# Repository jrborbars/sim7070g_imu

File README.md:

# sim7070g_imu
Sim7070g custom board with imu + batt

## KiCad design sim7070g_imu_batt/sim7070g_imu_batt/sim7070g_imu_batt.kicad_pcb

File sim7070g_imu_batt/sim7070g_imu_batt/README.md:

# sim7070g_imu_batt — build outputs (regenerate, do not hand-edit)

This folder holds circuit-synth outputs for the 45x35mm daughterboard:
SIM7070G OpenCPU + LSM6DSV16X + ETA6095 (~1A) + 1S LiPo solder pads.

## Regenerate (from repo root, project .venv = Python 3.14.x, no pins)

KICAD_SYMBOL_DIR="./sim7070g_imu_batt:/Applications/KiCad/KiCad.app/Contents/SharedSupport/symbols" \
./.venv/bin/python -c "import sim7070g_imu_batt.board as b; c=b.board(); c.generate_kicad_netlist('sim7070g_imu_batt/sim7070g_imu_batt.net'); print(c.generate_text_netlist()[:2000])"

BOM:

KICAD_SYMBOL_DIR="./sim7070g_imu_batt:/Applications/KiCad/KiCad.app/Contents/SharedSupport/symbols" \
./.venv/bin/python -c "import sim7070g_imu_batt.board as b; c=b.board(); print(c.generate_bom(project_name='sim7070g_imu_batt'))"

## KiCad workflow (schematic-first, OSS synth has no licensed PCB gen)

Workaround baked into `main.py` (`ensure_pin_number_preference`, runs on
every generation): upstream `circuit_synth/kicad/sch_gen/circuit_loader.py`
identifies pins by NAME first; stock C/R/L pins have empty names and power
pins repeat names, collapsing labels onto pin 1 (102 shorts/floats in KiCad's
own netlist, e.g. C1.1 VBAT->GND). `main.py` rewrites the installed loader
(idempotent no-op once upstream fixes it) to prefer pin NUMBER; after that
KiCad's netlist matches circuit-synth's on all 164 pins (0 real problems,
verified with `kicad-cli sch export netlist` + `cmp_netlists.py`).
Re-create the venv any time (Python 3.14.x, unpinned, pip resolves) — the
fix re-applies automatically. Only GND is exempted from power-symbol
rendering (`Net("GND", is_power=False)` in `board.py`) because the GND
symbol carries no connection semantics beyond the label here.

1. Open `sim7070g_imu_batt.kicad_pro` in KiCad.
2. Symbol libs (`sym-lib-table`): sim7070g / eta6095 / lsm6dsv16x (local
   `.kicad_sym` in this folder) + KiCad stock. Footprints (`fp-lib-table`):
   `footprints.pretty/` (local) + KiCad stock.
3. `LSM6DSV16X_LGA14.kicad_mod` is real geometry from SnapEDA
   XDCR_LSM6DSV16XTR as built in lsm6dsv16x-xiao (verify vs ST datasheet
   mech table before fab).
4. `*_PLACEHOLDER.kicad_mod` files are DO-NOT-FAB outlines only. Draw true
   `SIM7070G_LCC_LGA68` (24x24mm 68-pin LCC+LGA + 0.3mm thermal-via array,
   tented/plugged, per SIM7070 HW Design V1.05), `NanoSIM_PushPush` (MPN
   pads + DET switch), `USB-C-16P` (MPN pads + shell), `BAT_SolderPads`
   (wire-gauge pads + NPTH strain relief) before layout, then replace the
   footprint links in `board.py`.
5. Import `sim7070g_imu_batt.net` into a new 4-layer board
   (L1 Sig / L2 GND continuous / L3 PWR / L4 Sig, 1.6mm FR4) sized 45x35mm
   with 0.6mm castellated edge (TXD/RXD, USB_DP/DM, PWRKEY, RESET_N, BOOT,
   CHG_STAT, BAT+, GND). Layout rules: VBAT 1uF+TVS <2mm then 2x100uF
   <10mm on 1.0-1.5mm copper; RF L1 ref L2, Pi at ANT (series 0R, shunts
   DNP), keepout 3xW, 50R width = TRACE_W_50R_MM tuned to fab + VNA;
   USB 90R dL<0.15mm; SIM module->ESDA6V1->holder <100mm, 100nF+22pF at
   VSIM, DET 10k PU DNP; I2C 4.7k to 1V8; INT via 0R DNP to wake GPIOs.

## Locked electrical facts

ETA6095 (datasheet V1.9, 8p): NO TS/NTC, NO JEITA, NO SYS/power-path.
ISET 0.8V (150k=1.2A, 82k=2A) -> 180k ~= 1A for 1000mAh 1C. CV 4.21V,
precond 2.9V/200mA, term 130mA, recharge -160mV, STAT low=chg/Hi-Z=done,
OTG=GND forces buck. SIM7070G VBAT tied to BAT node for 2A bursts.
VDDIO=1.8V from VDD_EXT reference. MAX17048 + NTC 10k footprints DNP.

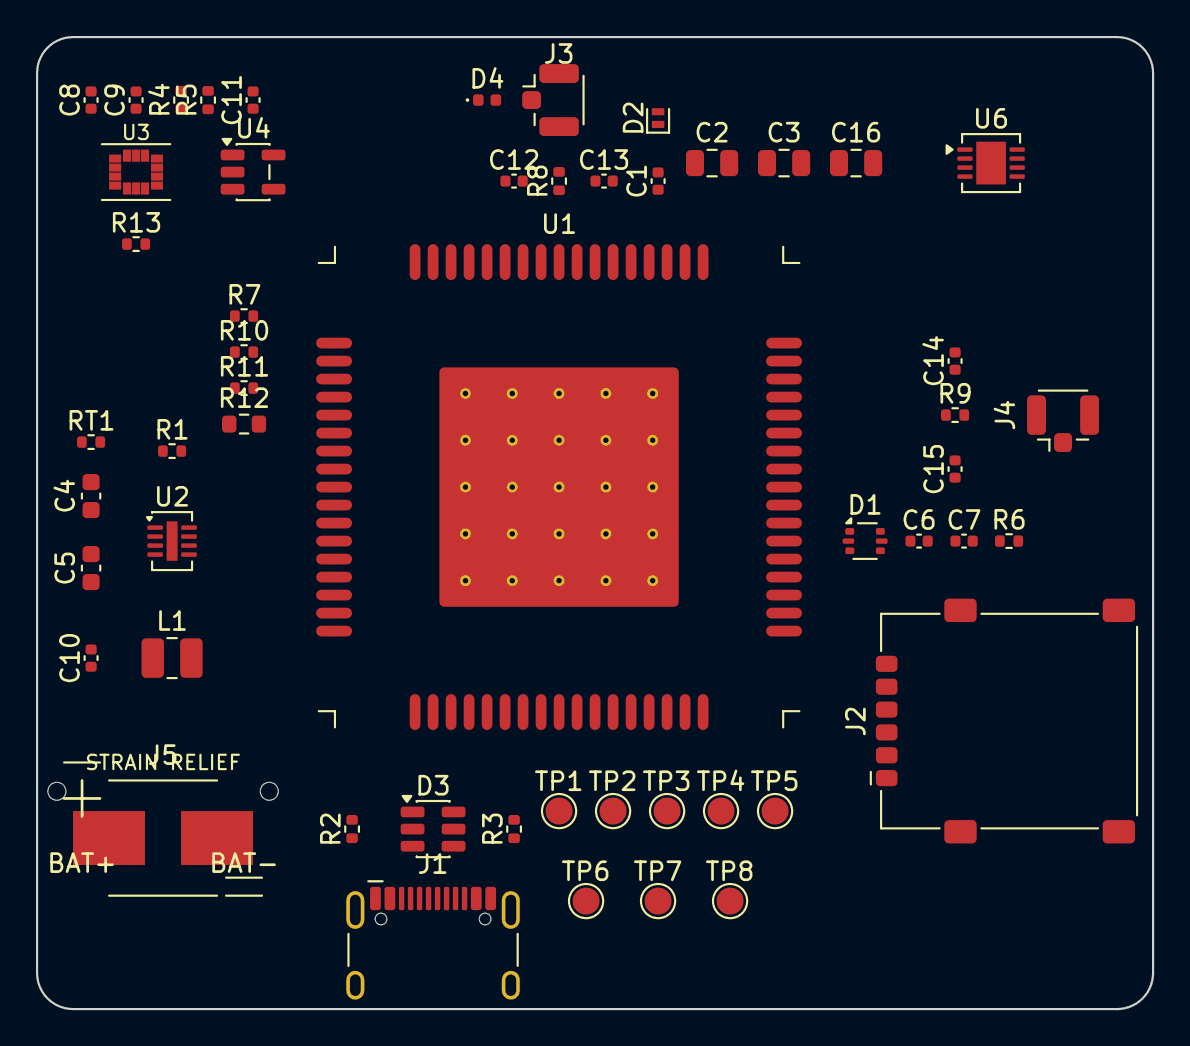
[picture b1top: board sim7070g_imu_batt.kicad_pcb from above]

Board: 4 copper layers, 62.0 x 54.0 mm, 53 parts (0 on the bottom side), 36 nets, no tracks yet.

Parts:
C1, C9, C10, C11: 1uF; C_0402_1005Metric
C2, C3, C16: 100uF; C_0805_2012Metric
C4, C5: 22uF; C_0603_1608Metric
C6, C8: 100nF; C_0402_1005Metric
C7: 22pF; C_0402_1005Metric
C12, C13, C14, C15: DNP_SHUNT; C_0402_1005Metric
D1: ESDA6V1; SOT-666
D2: TVS_PESDHC2FD4V5B; D_SOD-882
D3: USBLC6-2P6; SOT-23-6
D4: TVS_LOWCAP_ANT; D_0402_1005Metric
J1: USB-C-16P; USB_C_Receptacle_HCTL_HC-TYPE-C-16P-01A
J2: NanoSIM; NanoSIM_GCT_SIM8060-6-1
J3: U.FL_LTE; U.FL_Hirose_U.FL-R-SMT-1_Vertical
J4: U.FL_GNSS; U.FL_Hirose_U.FL-R-SMT-1_Vertical
J5: BAT_SOLDER_PADS; BAT_SolderPads
L1: 2.2uH; L_1008_2520Metric
R1: 180k; R_0402_1005Metric
R2, R3: 5.1k; R_0402_1005Metric
R4, R5: 1k; R_0402_1005Metric
R6, R13: 10k; R_0402_1005Metric
R7: 0R_JMP_GND; R_0402_1005Metric
R8, R9, R10, R11: 0R; R_0402_1005Metric
R12: 0R; R_0603_1608Metric
RT1: NTC_10k_B3380; R_0402_1005Metric
TP1: TP_PWRKEY; TestPoint_Pad_D1.5mm
TP2: TP_UART1_TXD; TestPoint_Pad_D1.5mm
TP3: TP_UART1_RXD; TestPoint_Pad_D1.5mm
TP4: TP_DEBUG_TXD; TestPoint_Pad_D1.5mm
TP5: TP_DEBUG_RXD; TestPoint_Pad_D1.5mm
TP6: TP_STATUS; TestPoint_Pad_D1.5mm
TP7: TP_CHG_STAT; TestPoint_Pad_D1.5mm
TP8: TP_VDD_EXT; TestPoint_Pad_D1.5mm
U1: SIM7070G; SIM7070G_LCC_LGA68
U2: ETA6095; DFN-8-1EP_2x3mm_P0.5mm_EP0.61x2.2mm
U3: LSM6DSV16X; LSM6DSV16X_LGA14
U4: NanoIq_LDO_2V5; SOT-23-5
U6: MAX17048_DNP; DFN-8-1EP_3x3mm_P0.5mm_EP1.65x2.38mm

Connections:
/ANT_GNSS: C14.1, R9.1, U1.53
/ANT_GNSS_MID: C15.1, J4.1, R9.2
/ANT_LTE: C12.1, D4.1, R8.1, U1.60
/ANT_LTE_MID: C13.1, J3.1, R8.2
/BAT_PACK: J5.1, R12.1
/BOOT_CFG: R7.1, U1.6
/CC1: J1.A5, R2.2
/CC2: J1.B5, R3.2
/CHG_STAT: TP7.1, U2.4
/DEBUG_RXD: TP5.1, U1.22
/DEBUG_TXD: TP4.1, U1.23
/GND: C1.2, C2.2, C3.2, C4.2, C5.2, C6.2, C7.2, C8.2, C9.2, C11.2, C12.2, C13.2, C14.2, C15.2, C16.2, D1.2, D2.2, D3.2, D4.2, J1.A1, J1.A12, J1.B1, J1.B12, J1.SH, J2.5, J2.6, J2.SH, J3.2, J4.2, J5.2, R1.2, R2.1, R3.1, R7.2, RT1.2, U1.2, U2.2, U2.6, U2.8, U3.6, U3.7, U4.2, U6.4
/IMU_VDD: C8.1, C9.1, C11.1, U3.8, U4.5
/INT1: R10.1, U3.4
/INT1_M: R10.2, U1.20
/INT2: R11.1, U3.9
/INT2_M: R11.2, U1.21
/ISET: R1.1, U2.3
/PWRKEY: TP1.1, U1.1
/SCL: R5.2, U1.38, U3.13, U6.6
/SDA: R4.2, U1.37, U3.14, U6.5
/SIM_CLK: D1.1, J2.3, U1.32
/SIM_DATA: D1.3, J2.7, U1.31
/SIM_DET: D1.6, J2.SW, R6.2, U1.67
/SIM_RST: D1.4, J2.2, U1.33
/STATUS: TP6.1, U1.66
/SW_CHG: L1.1, U2.7
/UART1_DTR: R13.2, U1.3
/UART1_RXD: TP3.1, U1.10
/UART1_TXD: TP2.1, U1.9
/USB_5V: C4.1, C5.1, D3.5, J1.A4, J1.A9, J1.B4, J1.B9, U1.24, U2.5
/USB_DM: D3.3, D3.4, J1.A7, J1.B7, U1.28
/USB_DP: D3.1, D3.6, J1.A6, J1.B6, U1.27
/VBAT: C1.1, C2.1, C3.1, C10.1, C16.1, D2.1, L1.2, R12.2, RT1.1, U1.55, U2.1, U4.1, U4.3, U6.3, U6.8
/VDD_1V8: R4.1, R5.1, R6.1, R13.1, TP8.1, U1.15, U3.5
/VSIM: C6.1, C7.1, D1.5, J2.1, U1.30

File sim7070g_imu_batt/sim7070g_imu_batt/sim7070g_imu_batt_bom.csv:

"Refs","Value","Footprint","Qty","DNP"
"C1","1uF","Capacitor_SMD:C_0402_1005Metric","1",""
"C2","100uF","Capacitor_SMD:C_0805_2012Metric","1",""
"C3","100uF","Capacitor_SMD:C_0805_2012Metric","1",""
"C4","22uF","Capacitor_SMD:C_0603_1608Metric","1",""
"C5","22uF","Capacitor_SMD:C_0603_1608Metric","1",""
"C6","100nF","Capacitor_SMD:C_0402_1005Metric","1",""
"C7","22pF","Capacitor_SMD:C_0402_1005Metric","1",""
"C8","100nF","Capacitor_SMD:C_0402_1005Metric","1",""
"C9","1uF","Capacitor_SMD:C_0402_1005Metric","1",""
"C10","1uF","Capacitor_SMD:C_0402_1005Metric","1",""
"C11","1uF","Capacitor_SMD:C_0402_1005Metric","1",""
"C12","DNP_SHUNT","Capacitor_SMD:C_0402_1005Metric","1","true"
"C13","DNP_SHUNT","Capacitor_SMD:C_0402_1005Metric","1","true"
"C14","DNP_SHUNT","Capacitor_SMD:C_0402_1005Metric","1","true"
"C15","DNP_SHUNT","Capacitor_SMD:C_0402_1005Metric","1","true"
"C16","100uF","Capacitor_SMD:C_0805_2012Metric","1",""
"D1","ESDA6V1","Package_TO_SOT_SMD:SOT-666","1",""
"D2","TVS_PESDHC2FD4V5B","Diode_SMD:D_SOD-882","1",""
"D3","USBLC6-2P6","Package_TO_SOT_SMD:SOT-23-6","1",""
"D4","TVS_LOWCAP_ANT","Diode_SMD:D_0402_1005Metric","1","true"
"J1","USB-C-16P","Connector_USB:USB_C_Receptacle_HCTL_HC-TYPE-C-16P-01A","1",""
"J2","NanoSIM","sim7070g_imu_batt:NanoSIM_GCT_SIM8060-6-1","1",""
"J3","U.FL_LTE","Connector_Coaxial:U.FL_Hirose_U.FL-R-SMT-1_Vertical","1",""
"J4","U.FL_GNSS","Connector_Coaxial:U.FL_Hirose_U.FL-R-SMT-1_Vertical","1",""
"J5","BAT_SOLDER_PADS","sim7070g_imu_batt:BAT_SolderPads","1",""
"L1","2.2uH","Inductor_SMD:L_1008_2520Metric","1",""
"R1","180k","Resistor_SMD:R_0402_1005Metric","1",""
"R2","5.1k","Resistor_SMD:R_0402_1005Metric","1",""
"R3","5.1k","Resistor_SMD:R_0402_1005Metric","1",""
"R4","1k","Resistor_SMD:R_0402_1005Metric","1",""
"R5","1k","Resistor_SMD:R_0402_1005Metric","1",""
"R6","10k","Resistor_SMD:R_0402_1005Metric","1",""
"R7","0R_JMP_GND","Resistor_SMD:R_0402_1005Metric","1","true"
"R8","0R","Resistor_SMD:R_0402_1005Metric","1",""
"R9","0R","Resistor_SMD:R_0402_1005Metric","1",""
"R10","0R","Resistor_SMD:R_0402_1005Metric","1","true"
"R11","0R","Resistor_SMD:R_0402_1005Metric","1","true"
"R12","0R","Resistor_SMD:R_0603_1608Metric","1",""
"R13","10k","Resistor_SMD:R_0402_1005Metric","1",""
"RT1","NTC_10k_B3380","Resistor_SMD:R_0402_1005Metric","1","true"
"TP1","TP_PWRKEY","TestPoint:TestPoint_Pad_D1.5mm","1",""
"TP2","TP_UART1_TXD","TestPoint:TestPoint_Pad_D1.5mm","1",""
"TP3","TP_UART1_RXD","TestPoint:TestPoint_Pad_D1.5mm","1",""
"TP4","TP_DEBUG_TXD","TestPoint:TestPoint_Pad_D1.5mm","1",""
"TP5","TP_DEBUG_RXD","TestPoint:TestPoint_Pad_D1.5mm","1",""
"TP6","TP_STATUS","TestPoint:TestPoint_Pad_D1.5mm","1",""
"TP7","TP_CHG_STAT","TestPoint:TestPoint_Pad_D1.5mm","1",""
"TP8","TP_VDD_EXT","TestPoint:TestPoint_Pad_D1.5mm","1",""
"U1","SIM7070G","sim7070g_imu_batt:SIM7070G_LCC_LGA68","1",""
"U2","ETA6095","Package_DFN_QFN:DFN-8-1EP_2x3mm_P0.5mm_EP0.61x2.2mm","1",""
"U3","LSM6DSV16X","sim7070g_imu_batt:LSM6DSV16X_LGA14","1",""
"U4","NanoIq_LDO_2V5","Package_TO_SOT_SMD:SOT-23-5","1",""
"U6","MAX17048_DNP","Package_DFN_QFN:DFN-8-1EP_3x3mm_P0.5mm_EP1.65x2.38mm","1","true"

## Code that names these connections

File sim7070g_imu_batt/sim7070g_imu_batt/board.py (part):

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
Facts that drive this schematic (all verified in the sources above)
------------------------------------------------------------------
* The SIM7070G has NO dedicated RESET pin: reset is a >12.6s PWRKEY
  long-press. There is also NO dedicated SIM_DET pin, so card detect
  must land on a GPIO.
* Pins 55/56/57 are all VBAT and 15 pads are GND; the footprint
  collapses them to pad numbers 55 and 2 so that one symbol pin drives
  each rail (standard practice for module footprints).
* "BOOT_CFG and GPIO1 cannot be pulled up" before normal power-up, so
  the IMU interrupts are NOT parked on GPIO1, and BOOT_CFG gets no
  pull-up (only a DNP jumper to GND plus a test point).
* GPIO/I2C/UART/USB logic is 1.8V; VDD_EXT (pin 15) is a 1.8V, 50mA
  reference only, so it biases the I2C pull-ups and the IMU VDDIO while
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    # We keep the USB-C, so USB lines break out through J1; these TPs
    # cover the UART/status handshake needed to flash and to debug a
    # hung OpenCPU application over AT commands.
    # NOTE: the SIM7070G has NO reset pin - a PWRKEY low pulse >12.6s is
    # the hardware reset, so PWRKEY is the "reset" breakout here.
    tp_pwrkey = Component(symbol="Connector:TestPoint", ref="TP1",
                          value="TP_PWRKEY",
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    modem["SIM_VDD"] += vsim
    esd_sim["IO4"] += vsim
    sim["VCC"] += vsim
    c_vs1[1] += vsim     # 100nF hard against the holder pins
    c_vs2[1] += vsim     # 22pF hard against the holder pins

    # Card detect: the SIM7070G has no SIM_DET pin, so the holder's
    # normally-open switch (SW shorts to GND on insert) pulls a GPIO
    # low; 10k pull-up to VDD_EXT holds it high when the card is out.
    simdet = Net("SIM_DET")
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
